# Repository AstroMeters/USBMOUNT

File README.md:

# USBMOUNT - EQmod  USB-C convertor
Control your mount directly from  computer. 

Skywatcher mounts are very popular among amateur astronomers due to their adorable price and good quality. In the GoTo versions, they are equipped with a hand control with which the user can find an object or perform basic service operations. However, these mounts can be connected to a computer and greatly expand its capabilities.

## How to use

### Connection
The USBMOUNT is connected instead of the hand control. It provides full mount functionality.

* **To computer:** It is simple :) Only connect USBMOUNT to computer with USB-C cable. You can use, for example, the one you use for your smartphone. `PC (pwr)` LED should appear. It is recommended to use a quality cable to ensure a permanent and high-quality connection. 
* **To mount:**  For connection to the assembly, the converter is equipped with an RJ45 connector. You can use a cable that you connect to the hand control or a direct Ethernet cable to connect. (If your mount have an RJ45 connector - see the table below). After successful connection to the assembly, the `MOUNT (pwr)` LED should light up. 

> It is expected that the mount is powered and switched on.

### Mounting
The expected installation is using 3M DualLock Reclosable Fastener. (It is included in the package.) For gluing it is necessary to first degrease the surface and after gluing, keep it pressed for some time

If you need to operate the USBMOUNT (EQmod) over long distances, it is better to prefer a longer cable on the telescope side (RJ45). You can use a standard (straight) ethernet cable here. I recommend a shielded one. The length of the USB should not exceed 5m. Even with a shorter cable, the USB connection may not work reliably. 

### LED indicators
USBMOUNT is equipted with 4 LED diods. Two red ones indicate the presence of power in coresponding (nearest) connector. Simply if it is connected. The other two orange diods show data transfer. `TX` indicating data from computer to your mount. The `RX` is in the opposite direction. 

### Installation of drivers
#### Linux
The USBMOUNT01 device is natively supported by nowdays linux computers, ensuring effortless setup and compatibility for users. Simply connect USBMOUNT01 to your Linux computer, and you're ready to use USBMOUNT01 converter with your favourite control software. For example Indi with Kstars. 

#### Windows

### Stellarium

### Kstars/Indi/Ekos

## Supported mounts

| Mount | Connector | Note |
|-----|-----|-----|
| EQ8 |  RJ45 | |
| AZ-EQ6 | RJ45 | |
| EQ6-R | RJ45 | |
| NEQ6  PRO | RJ45 | |
| EQ6 Pro |  RJ45 | |
| EQ6 Synscan  | | |
| HEQ5 SynScan |  RJ45 | |
| HEQ5 SynTreck | RJ45 | |
| EQ5 Synscan | RJ45 | |
| EQ4 with Synscan (EQ5) | | |
| EQ3-2 with Synscan	 | | |
> The list may not be complete

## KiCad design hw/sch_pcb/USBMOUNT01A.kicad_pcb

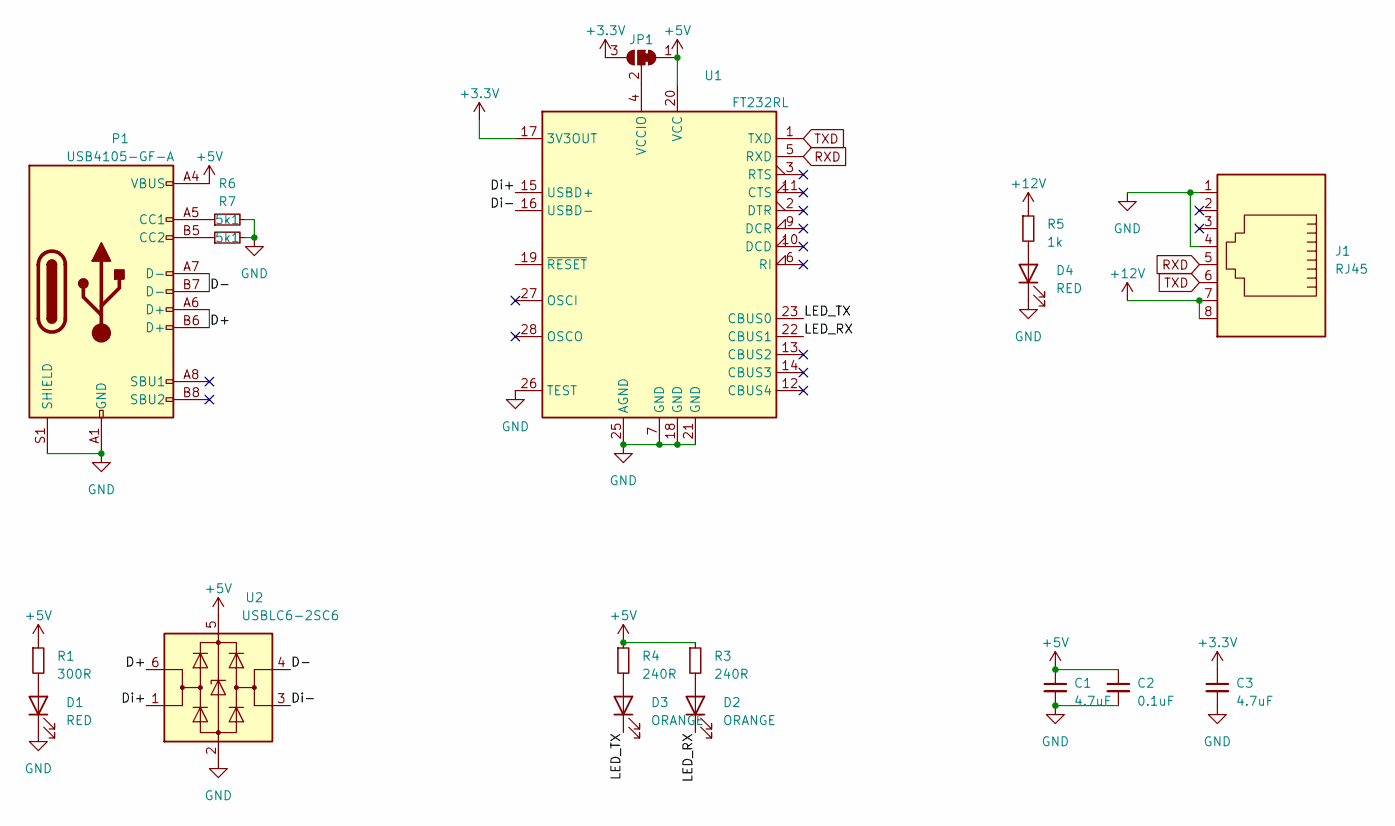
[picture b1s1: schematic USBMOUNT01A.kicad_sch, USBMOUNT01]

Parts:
C1, C3: 4.7uF; C_0805_2012Metric_Pad1.18x1.45mm_HandSolder; LCSC C1623
C2: 0.1uF; C_0805_2012Metric_Pad1.18x1.45mm_HandSolder; LCSC C1525
D1, D4: RED; LED_1206_3216Metric_ReverseMount_Hole1.8x2.4mm
D2, D3: ORANGE; LED_1206_3216Metric_ReverseMount_Hole1.8x2.4mm
J1: RJ45; RJ45_OST_PJ012-8P8CX_Vertical
JP1: SolderJumper_3_Bridged12; SolderJumper-3_P1.3mm_Bridged12_RoundedPad1.0x1.5mm
P1: USB4105-GF-A; USB_C_Receptacle_Palconn_UTC16-G; digikey 2073-USB4105-GF-ACT-ND
R1: 300R; R_0805_2012Metric_Pad1.20x1.40mm_HandSolder; LCSC C17617
R3, R4: 240R; R_0805_2012Metric_Pad1.20x1.40mm_HandSolder; LCSC C17572
R5: 1k; R_0805_2012Metric_Pad1.20x1.40mm_HandSolder; LCSC C17513
R6, R7: 5k1; R_0805_2012Metric_Pad1.20x1.40mm_HandSolder; LCSC C27834
U1: FT232RL; SSOP-28_5.3x10.2mm_P0.65mm; LCSC C8690
U2: USBLC6-2SC6; SOT-23-6; LCSC C7519

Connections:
+3V3: C3.1, JP1.3 (B), U1.17 (3V3OUT)
+5V: C1.1, C2.1, JP1.1 (A), P1.A4 (VBUS), P1.A9 (VBUS), P1.B4 (VBUS), P1.B9 (VBUS), R1.1, R3.1, R4.1, U1.20 (VCC), U2.5 (VBUS)
+12V: J1.7, J1.8, R5.1
/D+: P1.A6 (D+), P1.B6 (D+), U2.6 (I/O1)
/D-: P1.A7 (D-), P1.B7 (D-), U2.4 (I/O2)
/Di+: U1.15 (USBD+), U2.1 (I/O1)
/Di-: U1.16 (USBD-), U2.3 (I/O2)
/LED_RX: D2.1 (K), U1.22 (CBUS1)
/LED_TX: D3.1 (K), U1.23 (CBUS0)
GND: C1.2, C2.2, C3.2, D1.1 (K), D4.1 (K), J1.1, J1.4, P1.A1 (GND), P1.A12 (GND), P1.B1 (GND), P1.B12 (GND), P1.S1 (SHIELD), R6.2, R7.2, U1.7 (GND), U1.18 (GND), U1.21 (GND), U1.25 (AGND), U1.26 (TEST), U2.2 (GND)
unnamed: D1.2 (A), R1.2
unnamed: D2.2 (A), R3.2
unnamed: D3.2 (A), R4.2
unnamed: D4.2 (A), R5.2
unnamed: JP1.2 (C), U1.4 (VCCIO)
unnamed: P1.A5 (CC1), R6.1
unnamed: P1.B5 (CC2), R7.1
RXD: J1.5, U1.5 (RXD)
TXD: J1.6, U1.1 (TXD)

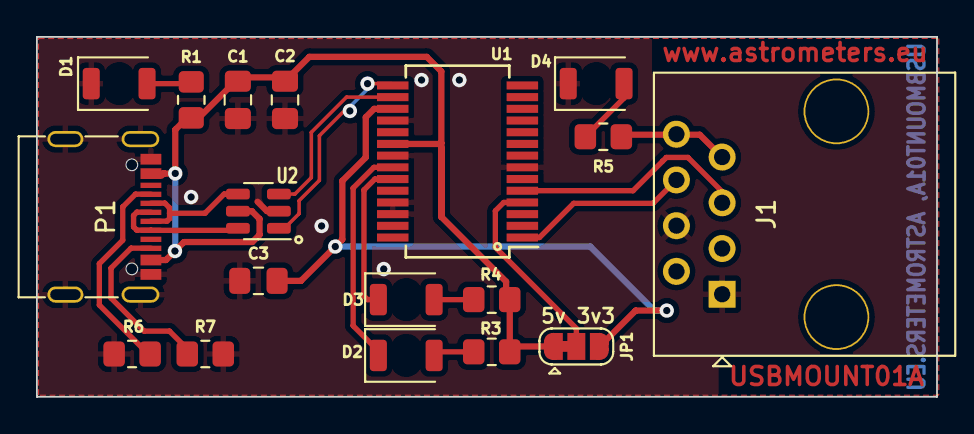
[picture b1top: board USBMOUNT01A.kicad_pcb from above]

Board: 2 copper layers, 50.0 x 20.0 mm, 18 parts (0 on the bottom side), 19 nets.

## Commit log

2021-04-18 New design
2021-04-18 manufacturing data
2021-04-30 minor changes
2022-11-20 add assets
2022-11-20 Update actions products
2022-11-22 update kicad version
2022-11-22 update assets
2023-06-19 resave to kicad7
2023-06-19 update actions
2023-06-19 aktualizace assets
2023-06-19 updater
2023-06-19 rename
2023-06-19 Update metadata files
2023-08-16 Update workflow files
